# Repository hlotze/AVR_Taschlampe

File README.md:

# AVR_Taschenlampe

Ein ATtiny2313 soll eine RGB-LED per PWM in ihrer Gesamtlichtfarbe beziehungsweise den Helligkeiten der einzelnen Farbkanäle steuern.

## Bedienanleitung

### Einschalten und Ausschalten

Den **ON-Taster drücken und gedrückt halten**. Die Taschenlampe leuchtet mit der zuletzt gespeicherten Farbe und Helligkeit. Bei der ersten Inbetriebnahme nach der Initialprogrammierung sind alle drei Farbkanäle auf den Wert 127 eingestellt.

Zum Ausschalten den ON-Taster loslassen. Nicht gespeicherte Änderungen gehen dabei verloren; beim nächsten Einschalten wird wieder die zuletzt gespeicherte Einstellung verwendet.

### Farbe und Helligkeit einstellen

Den ON-Taster während der gesamten Einstellung gedrückt halten. Die drei Farbkanäle lassen sich unabhängig voneinander verändern:

| Farbkanal | Heller | Dunkler |
|---|---|---|
| Rot | INC_rt | DEC_rt |
| Grün | INC_gn | DEC_gn |
| Blau | INC_bl | DEC_bl |

Ein kurzer Tastendruck erhöht beziehungsweise verringert den jeweiligen Helligkeitswert um 4. Zur Rückmeldung wird der geänderte Farbkanal kurz für etwa 15 ms ausgeschaltet; danach ist seine neue Helligkeit sichtbar. Wird die Taste länger gehalten, beginnt nach etwa einer halben Sekunde die automatische Wiederholung mit ungefähr zehn Änderungen pro Sekunde.

Würde der nächste Schritt über 255 oder unter 0 führen, wird genau der jeweilige Grenzwert erreicht: INC setzt beispielsweise 253 auf 255, DEC setzt 2 auf 0. Damit lässt sich jede Farbe vollständig ausschalten oder auf maximale Helligkeit stellen. Am Grenzwert bleibt der Kanal auch bei weiterem Halten oder erneutem Drücken derselben Taste stehen. Die entgegengesetzte Taste verändert ihn wieder um 4: von 0 auf 4 beziehungsweise von 255 auf 251.

Mehrere Farbkanäle können gleichzeitig eingestellt werden. Werden INC und DEC desselben Kanals gleichzeitig gedrückt, bleibt dieser Kanal unverändert.

Bei jeder tatsächlichen Wertänderung – auch bei automatischer Wiederholung – erhält nur der betroffene Farbkanal diesen kurzen Dunkelimpuls. Andere Farbkanäle bleiben sichtbar. Ist der Endwert bereits erreicht und ändert sich nichts, erfolgt kein weiterer Impuls. Tasterauswertung und Speicherung laufen unabhängig davon weiter; STORE hat Vorrang und behält seine Doppelblinkbestätigung.

### Einzelne Farben beim Einstellen anzeigen

Mit dem Jumper **JP1 (SOLO)** zwischen **PB0, Pin 12, und GND** lässt sich die Anzeige beim Einstellen umschalten:

| JP1 | Anzeige während INC/DEC |
|---|---|
| Offen | Die vollständige Farbmischung bleibt sichtbar. |
| Gesteckt | Nur die Farbkanäle mit gedrückten Einstelltasten sind sichtbar. |

Beispiel: Bei gestecktem JP1 blendet das Halten von INC_rt oder DEC_rt Grün und Blau aus. Rot bleibt sichtbar und wird eingestellt. Sobald die letzte Einstelltaste losgelassen und deren Freigabe entprellt wurde, erscheint wieder die vollständige Mischung mit dem neuen Rotwert. Die Werte der ausgeblendeten Kanäle bleiben erhalten.

Werden mehrere Farbkanäle gleichzeitig eingestellt, sind diese gemeinsam sichtbar. Bei gleichzeitigem INC und DEC eines Kanals bleibt dieser sichtbar, aber sein Wert unverändert. Das Ausblenden funktioniert auch dann, wenn der bearbeitete Kanal bereits seinen Grenzwert erreicht hat. Tasten, die beim Einschalten gehalten und noch nicht freigegeben wurden, lösen keine Einzelanzeige aus.

Der Jumper wird laufend ausgewertet und kann während des Betriebs geändert werden. STORE speichert unabhängig vom Modus immer die tatsächlichen Werte aller drei Farbkanäle. Die Doppelblinkbestätigung verwendet weiterhin alle drei Farben.

### Einstellung speichern

1. Die gewünschte Farbe und Helligkeit einstellen und die Einstelltasten loslassen. ON weiterhin gedrückt halten.
2. **STORE einmal drücken**.
3. Die Bestätigung abwarten: Die LED blinkt zweimal mit der vorgesehenen Weißmischung und zeigt danach wieder die eingestellte Farbe. ON bis zum Ende dieser Bestätigung gedrückt halten.
4. Anschließend kann ON losgelassen werden. Die Einstellung wird beim nächsten Einschalten wiederhergestellt.

Wenn die aktuelle Einstellung bereits gespeichert ist, bewirkt STORE keine erneute Speicherung und die LED blinkt nicht. Längeres Gedrückthalten von STORE löst keine zusätzlichen Speichervorgänge aus.

Während des Speicherns und Blinkens werden die Bedientasten ignoriert. Für weitere Änderungen gegebenenfalls noch gehaltene Einstelltasten oder STORE zuerst loslassen und erneut drücken. Das gilt auch für Tasten, die bereits beim Einschalten gehalten wurden.

### Test auf dem Evaluationboard

Diese Bedienanleitung beschreibt die eigenständig versorgte Taschenlampe. Beim Test mit dem ATtiny auf dem Evaluationboard schaltet der ON-Taster am Steckbrett nur die LED-Versorgung. Der Mikrocontroller läuft weiter; das Einschalten mit erneutem Laden der gespeicherten Werte wird dort durch einen Reset am Evaluationboard getestet. Anschluss- und Programmierhinweise stehen in der [Firmware-Anleitung](firmware/README.md).

## Funktion

### Stromversorgung

Die Schaltung wird mit drei AAA-Batterien zu je 1,5 V betrieben. Die Nennspannung beträgt somit 4,5 V.

### ON Taster

Der ON-Taster schließt den positiven 4,5-V-Zweig und versorgt die gesamte Schaltung einschließlich des ATtiny2313 mit Spannung. Die Taschenlampe leuchtet nur, solange der ON-Taster gehalten wird.

Beim Einschalten werden die Helligkeitswerte für Rot, Grün und Blau aus dem internen EEPROM gelesen und gemäß den unter „internes EEPROM“ beschriebenen Regeln geprüft. Die Einzel-LEDs erhalten die entsprechenden PWM-Signale. Lichtblitze beim Einschalten sollen vermieden werden.

Nach dem Einschalten wird ausschließlich die gespeicherte beziehungsweise bei einem Speicherfehler die vorgesehene Ersatzhelligkeit des jeweiligen Farbkanals ausgegeben; vorher bleiben alle Farbkanäle aus.

Beim Einschalten bereits gedrückte INC-, DEC- und STORE-Taster werden erst nach dem Loslassen und einem erneuten Drücken ausgewertet.

Beim Loslassen des ON-Tasters erlischt die LED. Änderungen, die nicht mit STORE gespeichert wurden, gehen verloren.

### Common-Anode LED

Die Common-Anode-LED besteht aus drei Einzel-LEDs mit gemeinsamer Anode: jeweils einer für Rot, Grün und Blau.

Der Helligkeitswert jedes Farbkanals liegt zwischen 0 (vollständig aus) und 255 (vollständig an).

Die PWM-Frequenz ist bei der Firmware-Konfiguration einstellbar. Ein durch eine zu niedrige PWM-Frequenz verursachtes Flimmern ist bei Bedarf durch Anpassen dieser Konfiguration zu beheben. Mit „Anwender“ ist hierbei die Person gemeint, die die Firmware konfiguriert und programmiert.

### Taster für Helligkeitswerte der Einzel-LEDs

Für jeden Farbkanal gibt es einen Taster zum Erhöhen (INC) und einen zum Verringern (DEC) der Helligkeit:

- INC_rt, DEC_rt
- INC_gn, DEC_gn
- INC_bl, DEC_bl

Alle Taster außer dem ON-Taster sind zu entprellen. Dies gilt auch für STORE.

Ein entprellter Tastendruck verändert den Helligkeitswert des jeweiligen Kanals sofort um +4 (INC) beziehungsweise −4 (DEC) Einheiten. Zur optischen Schrittrückmeldung wird die PWM-Ausgabe nur dieses Kanals für etwa 15 ms auf 0 gesetzt und anschließend der neue Wert ausgegeben. Die Rückmeldung blockiert die Tasterauswertung nicht und wird nur bei einer tatsächlichen Wertänderung ausgelöst.

Die Helligkeit wird in Schritten von ±4 verändert und auf den Wertebereich 0 bis 255 begrenzt. Würde INC über 255 hinausführen, wird auf 255 gesetzt; würde DEC unter 0 führen, wird auf 0 gesetzt. Der letzte Schritt darf dadurch kleiner als 4 sein. Beispiele: INC verändert 253 auf 255, DEC verändert 2 auf 0. Auch ausgehend vom Startwert 127 werden beide Endwerte erreicht. Weiteres Halten oder erneutes Drücken derselben Taste lässt den Grenzwert unverändert. Die Gegenrichtung arbeitet von dort mit einem vollen Schritt weiter: INC von 0 auf 4, DEC von 255 auf 251. Es erfolgt kein Umlauf.

Nach 500 ms Gedrückthalten wird die Änderung alle 100 ms wiederholt, bis die Taste losgelassen wird.

Verschiedene Farbkanäle lassen sich gleichzeitig einstellen. Sind INC und DEC desselben Kanals gleichzeitig gedrückt, bleibt dieser Kanal unverändert; andere Kanäle werden weiterhin ausgewertet.

### Jumper für die Einzelkanalanzeige

JP1 verbindet PB0 (DIP-Pin 12) mit GND. Der Eingang nutzt den internen Pull-up; offen entspricht HIGH und der bisherigen Mischanzeige, gesteckt entspricht LOW und der Einzelkanalanzeige während INC/DEC. PB1 bleibt frei.

Die Firmware wertet JP1 in jedem Bedienzyklus aus. Bei gestecktem JP1 werden nur Kanäle mit entprellten, freigegebenen und gehaltenen INC-/DEC-Tasten ausgegeben; alle übrigen PWM-Ausgänge werden vorübergehend auf 0 gesetzt. Ohne aktive Einstelltaste wird die volle Mischung ausgegeben. Die zugrunde liegenden RGB-Werte werden durch diese Anzeigeauswahl nicht verändert. Speichern und Blinkbestätigung behalten Vorrang; danach gelten weiterhin die Regeln zur erneuten Tastenfreigabe.

### Store Taster

Der STORE-Taster dient zum dauerhaften Speichern der aktuellen Helligkeitswerte für Rot, Grün und Blau im internen EEPROM. Erst nach dem Speichern stehen geänderte Werte beim nächsten Einschalten wieder zur Verfügung.

Beim Drücken von STORE werden die aktuellen Werte aller drei Kanäle als gemeinsamer Stand übernommen. Falls gleichzeitig eine Helligkeitsänderung erkannt wird, wird zuerst diese Änderung ausgeführt und anschließend gespeichert.

Die Speicherung wird nur ausgelöst, wenn sich aktuelle Werte von den gespeicherten Werten unterscheiden. Stimmen alle Werte überein, wird weder geschrieben noch eine Blinkbestätigung ausgegeben. Für ungültige EEPROM-Einträge gilt die unter „internes EEPROM“ beschriebene Ausnahme.

Pro Tastendruck wird höchstens einmal gespeichert und einmal durch doppeltes Blinken bestätigt, auch wenn STORE länger gedrückt bleibt.

Während des Speicherns und der Blinkbestätigung werden INC, DEC und STORE ignoriert. Danach werden noch gehaltene Tasten erst nach dem Loslassen und erneutem Drücken ausgewertet.

Nach erfolgreichem Speichern blinkt die LED zweimal weiß mit RGB (127, 127, 127): jeweils 200 ms an und 200 ms aus. Die Bestätigung funktioniert dadurch auch bei zuvor ausgeschalteten Farbkanälen. Danach werden die aktuellen Helligkeitswerte wieder angezeigt.

Der ON-Taster muss bis zum Ende der Bestätigung gehalten werden. Anschließend kann er losgelassen werden; die neuen Werte sind gespeichert und werden beim nächsten Einschalten verwendet.

### internes EEPROM

Bei der Programmierung des ATtiny2313 werden die initialen Helligkeitswerte im internen EEPROM auf RGB (127, 127, 127) festgelegt.

Beim Einschalten werden die gespeicherten Werte pro Kanal auf Gültigkeit geprüft. Ein fehlender oder als ungültig erkennbarer Kanalwert wird nur für diesen Kanal durch den Standardwert 127 ersetzt. Sind alle drei Werte ungültig, ergibt sich RGB (127, 127, 127).

Nach einem unterbrochenen Speichervorgang wird mit den vorliegenden gültigen EEPROM-Werten gearbeitet. Dabei dürfen gültige alte und neue Kanalwerte gemeinsam verwendet werden. Ein unvollständig geschriebener oder beschädigter Kanalwert muss als ungültig erkennbar sein und wird durch 127 ersetzt. Der Zahlenwert 255 allein gilt nicht als Fehler, da er zum erlaubten Wertebereich gehört.

Ersatzwerte werden zunächst nur für den laufenden Betrieb verwendet. Erst ein erneuter STORE-Tastendruck speichert sie dauerhaft. Dabei gilt ein ungültiger EEPROM-Eintrag als Abweichung, auch wenn der Ersatzwert bereits 127 beträgt.

## Umsetzung

### Schaltplan

[KiCad-Schaltplan](hardware/AVR_Taschenlampe.kicad_sch) auf DIN A4 im Querformat, [KiCad-Projekt](hardware/AVR_Taschenlampe.kicad_pro) und [Vorschau](hardware/preview/AVR_Taschenlampe.svg).

Details zu Pinbelegung, Bauteilen, LED-Auswahl und Prüfung stehen in der [Schaltungsdokumentation](hardware/README.md).

### Platinenlayout

[Belegungsplan für 24 × 18 Löcher im Hochformat](hardware/lochraster-24x18-hochformat.md) mit Lochkoordinaten und Drahtliste. Die [Zeichnung](hardware/lochraster-24x18-hochformat.svg) zeigt die Bestückungsseite, die gespiegelte Lötseite und den Drahtverlauf von oben. Zum Umplatzieren und Entflechten gibt es ein [editierbares KiCad-Board](hardware/lochraster-24x18-hochformat.kicad_pcb).

### Codierung

[Firmware und Anleitung zum Bauen und Programmieren](firmware/README.md), [Programmcode](firmware/src/main.c).

Die erste Version für den ATtiny2313 enthält RGB-PWM, Tasterbedienung und EEPROM-Speicherung. Flash- und EEPROM-Dateien werden getrennt erzeugt; Am 16.11.2026 hat der Anwender auf dem Evaluationboard die Helligkeitsänderung je Farbkanal über INC/DEC, das Speichern mit STORE einschließlich Doppelblinken sowie die Wiederherstellung der zuletzt gespeicherten Farbe nach RESET erfolgreich geprüft.

## Programmierung und Testaufbau 

- mit Pollin Evaluationboard und Portsplitter
  - ATtiny2313
  - RGB-LED, jede Farbe wird über eigenen Transistor angesteuert
  - 6 Taster für INC & DEC der Helligkeit jeder Farbe rot, grün, blau
  - Store-Taster, zum Speicher der Helligkeitswerte in ATtiny internen EEPROM

## weitere Dokumentation

siehe im Verzeichnis [docs](docs/docs.md)

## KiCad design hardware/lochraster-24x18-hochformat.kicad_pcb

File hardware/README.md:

# Schaltplan AVR-Taschenlampe

Der Schaltplan liegt im nativen KiCad-Format auf einem A4-Blatt im Querformat vor. Das Projekt wurde mit KiCad 10.0.8 erstellt.

- [KiCad-Projekt](AVR_Taschenlampe.kicad_pro)
- [Editierbarer Schaltplan](AVR_Taschenlampe.kicad_sch)
- [A4-Vorschau als SVG](preview/AVR_Taschenlampe.svg)
- [A4-Vorschau als PNG, 300 dpi](preview/AVR_Taschenlampe.png)
- [Elektrische Regelprüfung](erc.json)
- [Exportierte Netzliste](AVR_Taschenlampe.net)

Gleiche Netzbezeichnungen verbinden die räumlich getrennten Schaltungsteile elektrisch. Die Symbole und Beschriftungen sind gegenüber der ersten Fassung um etwa 30 % vergrößert. Die vergrößerten Symbole liegen in der Projektbibliothek `Taschenlampe.kicad_sym` und sind zusätzlich im Schaltplan eingebettet. Ihre Anschlussenden liegen weiterhin auf dem üblichen 50-mil-Raster. Die Bibliothekstabellen verwenden die Standardvariablen von KiCad 10.

## Aufbau

BT1 ist der Anschluss für drei AAA-Zellen in Reihe. SW1 (ON) schaltet ausschließlich den positiven Versorgungszweig. C1 (100 nF) gehört beim Layout unmittelbar an VCC und GND von U1; C2 (1 µF, ungepolt) puffert zusätzlich. Es gibt keine Selbsthaltung der Versorgung.

U1 ist ein ATtiny2313-20PU im DIP-20-Gehäuse. Das eingebettete KiCad-Symbol ATtiny2313V-10P besitzt dieselbe DIP-Pinbelegung; der Bestückungswert bezeichnet den vorgesehenen ATtiny2313-20PU. Der interne RC-Oszillator wird auf 1 MHz konfiguriert; ein externer Quarz ist nicht vorgesehen. Brown-out-Erkennung auf 2,7 V aktivieren, RESET und ISP aktiviert lassen, CKOUT deaktiviert lassen. Die konkreten Fuse-Bytes sind bei der Firmware-Erstellung anhand der tatsächlich eingesetzten Variante festzulegen.

D1 ist eine kleine RGB-LED mit gemeinsamer Anode. Q1–Q3 (BC547B) schalten deren Kathoden gegen Masse. Jede Farbe besitzt einen eigenen Vorwiderstand. Die Basispulldowns R8–R10 halten die Treiber auch während Reset und Programmierung ausgeschaltet. Die Firmware muss die PWM-Ausgänge vor der Aktivierung auf LOW setzen; ein HIGH-Pegel schaltet die jeweilige Farbe ein.

## Pinbelegung

| Funktion | Port | DIP-Pin |
|---|---|---:|
| Rot PWM | PB4 / OC1B | 16 |
| Grün PWM | PB3 / OC1A | 15 |
| Blau PWM | PB2 / OC0A | 14 |
| INC_rt | PD0 | 2 |
| DEC_rt | PD1 | 3 |
| INC_gn | PD2 | 6 |
| DEC_gn | PD3 | 7 |
| INC_bl | PD4 | 8 |
| DEC_bl | PD5 | 9 |
| STORE | PD6 | 11 |
| JP1 / SOLO | PB0 | 12 |
| RESET | PA2 | 1 |
| ISP MOSI | PB5 | 17 |
| ISP MISO | PB6 | 18 |
| ISP SCK | PB7 | 19 |
| VCC / GND | – | 20 / 10 |

Die sieben Bedientaster SW2–SW8 schalten gegen Masse. Interne Pull-ups aktivieren; gedrückt entspricht LOW. Entprellung, Wiederholung und die Behandlung gleichzeitig gedrückter Tasten erfolgen in der Firmware. Die ISP-Leitungen werden nicht durch Taster oder LED-Treiber belastet.

Timer 0 liefert Blau. Timer 1 liefert Grün und Rot und muss dafür im 8-Bit-PWM-Modus betrieben werden. Die Einstellung von PWM-Frequenz und Endwerten 0/255 ist Aufgabe der Firmware.

## JP1 / SOLO

JP1 besitzt zwei Pins: 1 = `SOLO_N` an U1/PB0 (DIP-Pin 12), 2 = GND. Der interne Pull-up wird in der Firmware aktiviert; es ist kein zusätzlicher Widerstand erforderlich. Offen bleibt die Mischung beim Einstellen sichtbar. Gesteckt werden während INC/DEC nur die bearbeiteten Farbkanäle angezeigt; nach Loslassen erscheint die Mischung wieder. Die RGB-Sollwerte bleiben erhalten, STORE speichert weiterhin alle drei Kanäle. Mehrere bearbeitete Kanäle sind gemeinsam sichtbar. Die Jumperstellung wird laufend ausgewertet. PB1 (Pin 13) bleibt unbeschaltet.

Für den Evaluationboard-Test PB0 am Portsplitter verwenden (Extension-Port J4, Pin 9) und JP1 gegen die gemeinsame Masse schalten. JP1 dieses Schaltplans ist nicht mit dem gleichnamigen UART-Jumper auf dem Pollin-Evaluationboard zu verwechseln.

## Bauteile und Dimensionierung

| Referenzen | Wert / Typ | Zweck |
|---|---|---|
| BT1 | 3 × AAA, nominell 4,5 V | Batteriehalteranschluss |
| SW1–SW8 | Schließertaster | ON und sieben Bedientaster |
| U1 | ATtiny2313-20PU | Steuerung, internes EEPROM |
| D1 | RGB, gemeinsame Anode | LED, konkreter Typ noch auszuwählen |
| Q1–Q3 | BC547B, C/B/E = Pins 1/2/3 | Kathodentreiber |
| R1 | 10 kΩ | RESET-Pull-up |
| R2–R4 | je 100 Ω, 0,25 W, 5 % oder besser | LED-Strombegrenzung |
| R5–R7 | je 1 kΩ | Basisstrombegrenzung |
| R8–R10 | je 100 kΩ | Basis-Emitter-Pulldown |
| C1 | 100 nF, Keramik, mindestens 10 V | Abblockung |
| C2 | 1 µF, Keramik, mindestens 10 V | Versorgungspuffer |
| J1 | AVR-ISP, 2 × 3, 2,54 mm | Programmierung |
| JP1 | Jumper, 1 × 2, 2,54 mm | Einzelkanalanzeige: PB0 nach GND |

Mit 100 Ω ergeben sich bei 4,5 V und angenommenen 0,2 V am Transistor rechnerisch etwa 23 mA für Rot bei 2,0 V LED-Durchlassspannung und 13 mA für Grün und Blau bei 3,0 V. Vor der Bestückung die zulässigen Ströme je Kanal anhand des LED-Datenblatts prüfen. Die tatsächlichen Ströme und die optische Weißmischung hängen vom LED-Typ ab.

Vor Bestückung sind LED-Typ, zulässige Ströme und Pinfolge festzulegen. Das Symbol nimmt 1 = Rot-Kathode, 2 = gemeinsame Anode, 3 = Grün-Kathode und 4 = Blau-Kathode an. Deshalb hat D1 noch keinen verbindlichen Footprint. Auch der Batteriehalter benötigt nach mechanischer Auswahl einen Footprint oder Anschluss. Die übrigen Footprints sind Vorschläge für bedrahtete Bauteile.

Der Mikrocontroller arbeitet bei 1 MHz im vorgesehenen Spannungsbereich; für den Entwurf wird eine Versorgung oberhalb der Brown-out-Schwelle bis etwa 4,8 V angenommen. Bei sinkender Batteriespannung nimmt die LED-Helligkeit ab; Grün und Blau können früher ausfallen. Eine geregelte, batteriezustandsunabhängige Helligkeit ist nicht vorgesehen.

## ISP und EEPROM

J1: 1 = MISO, 2 = VCC_SW, 3 = SCK, 4 = MOSI, 5 = RESET, 6 = GND. Beim Programmieren ON gedrückt halten. Der Programmer muss die Zielspannung berücksichtigen und darf die Schaltung nicht zusätzlich versorgen. Mit langsamem ISP-Takt beginnen, beispielsweise 125 kHz bei 1 MHz CPU-Takt.

Es gibt keinen Versorgungspuffer, der einen vollständigen EEPROM-Schreibvorgang nach Loslassen von ON garantiert. Die Firmware muss deshalb die vereinbarte Behandlung unterbrochener Schreibvorgänge umsetzen: pro Kanal einen prüfbaren Datensatz vorsehen, gültige alte/neue Werte zulassen und ungültige Werte durch 127 ersetzen. Eine Integritätsprüfung erkennt Fehler nur entsprechend ihrer Prüfstärke; eine absolute Erkennung beliebiger Beschädigungen ist nicht garantiert. Die Schaltung allein stellt diese Softwareanforderung nicht sicher.

## Prüfung und Grenzen

KiCad ERC: **0 Fehler und 0 Warnungen**, ohne ausgeschlossene Meldungen. Die exportierte Netzliste wurde mit `python3 tools/check_netlist.py` aus dem Projektverzeichnis gegen die beabsichtigten Pin-Netz-Zuordnungen geprüft. Die A4-Vorschau wurde visuell kontrolliert. Der Anwender hat am 16.11.2026 INC/DEC, STORE mit Doppelblinken und die Wiederherstellung nach RESET am Evaluationboard bestätigt. Die am 17.11.2026 ergänzte JP1-Funktion ist noch nicht am Aufbau getestet; elektrische Messungen und eine Schaltungssimulation stehen ebenfalls aus. Ein Platinenlayout ist nicht Bestandteil dieses Schaltplans.

Quellen: [Microchip ATtiny2313/V Datenblatt](https://ww1.microchip.com/downloads/en/DeviceDoc/Atmel-2543-AVR-ATtiny2313_Datasheet.pdf), [onsemi BC547-Datenblatt](https://www.onsemi.com/pdf/datasheet/bc546-d.pdf).

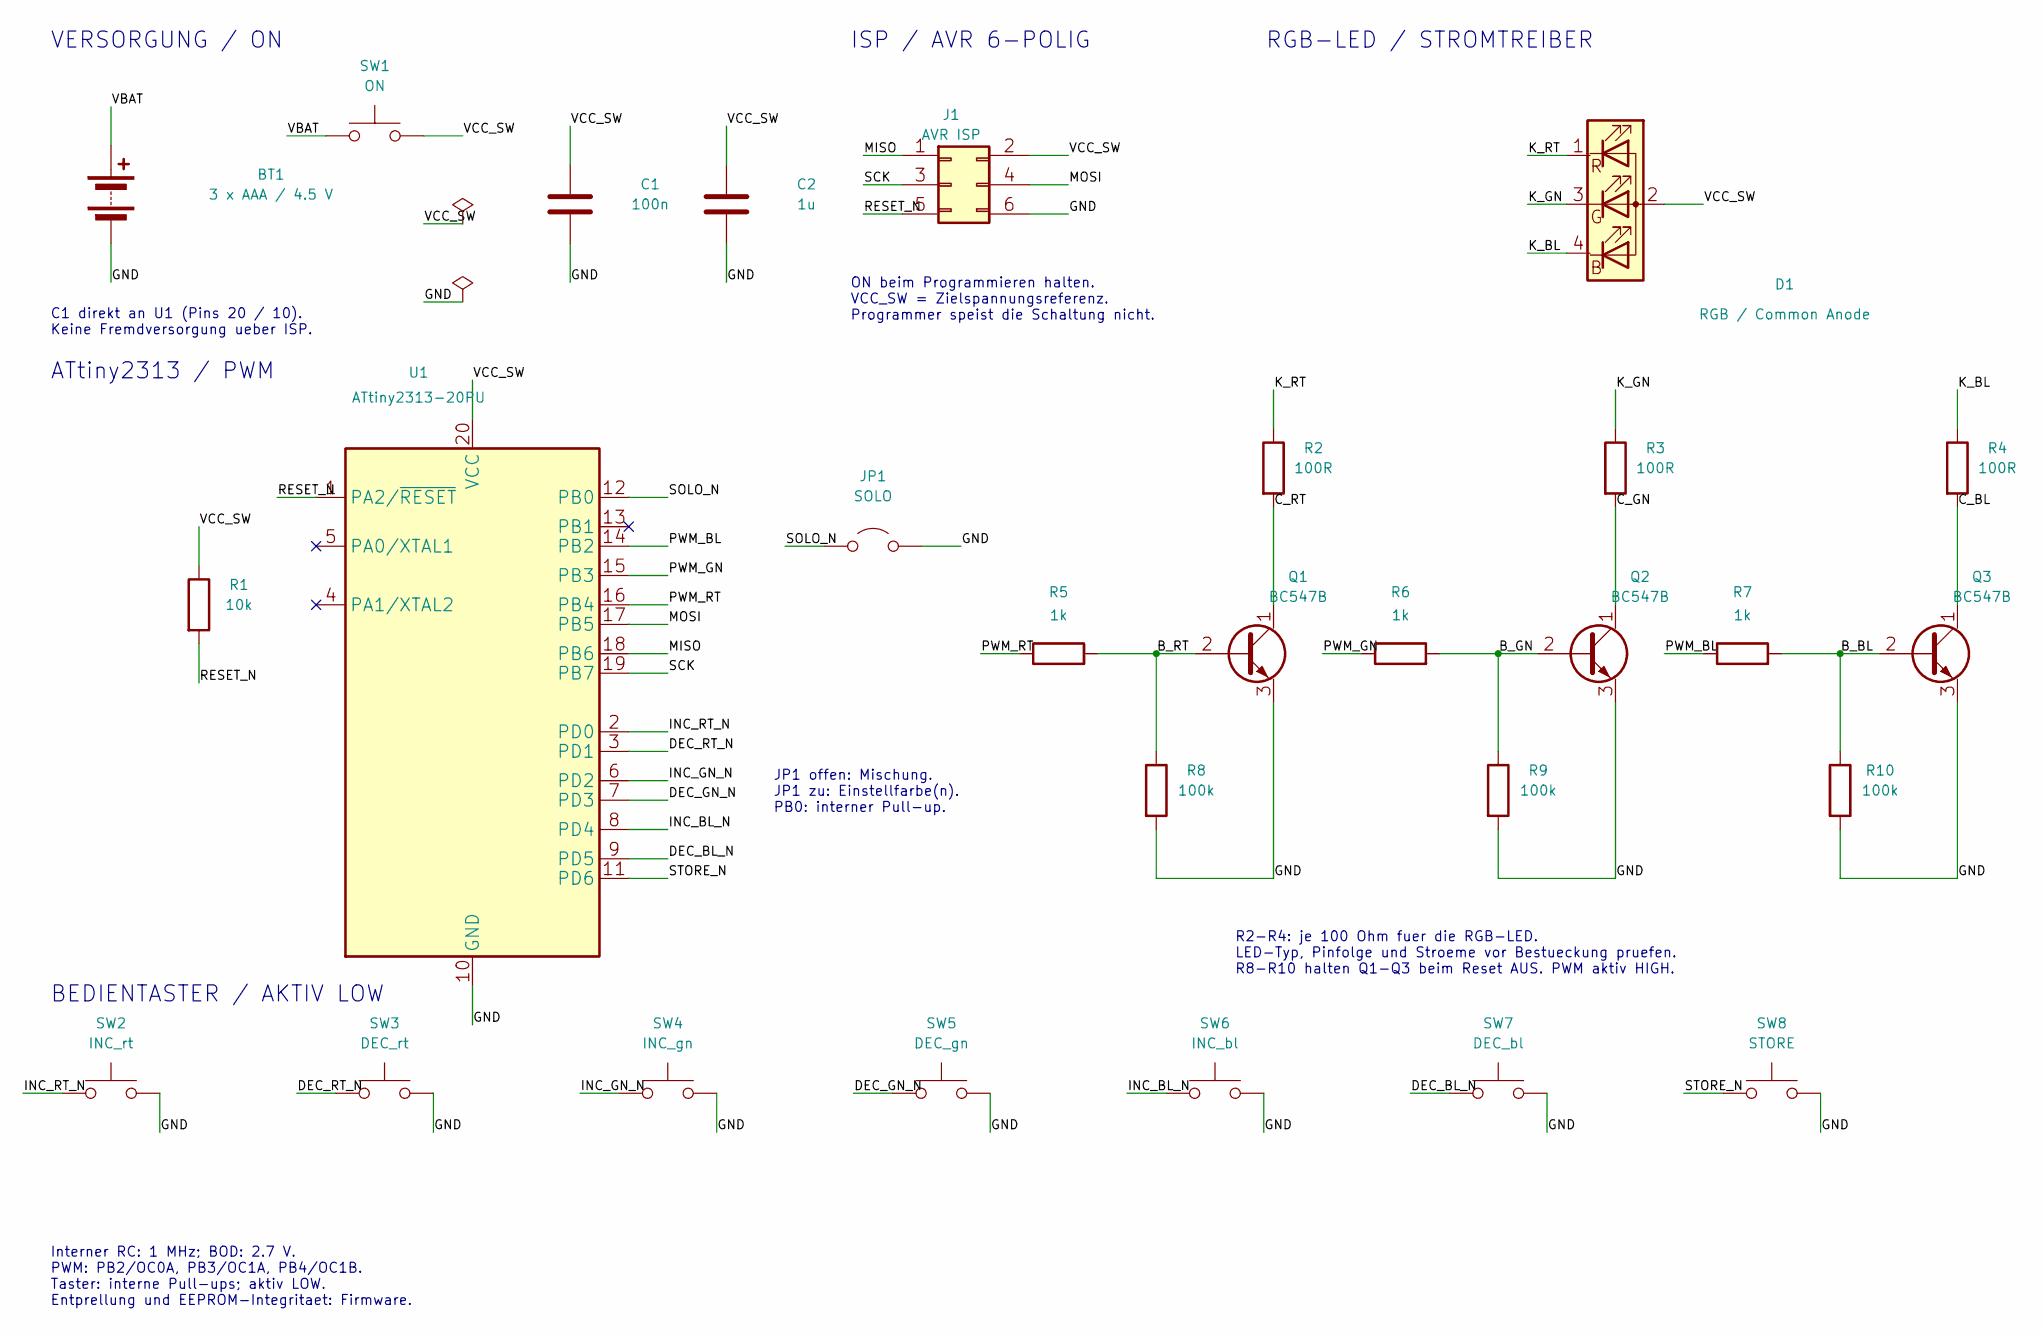
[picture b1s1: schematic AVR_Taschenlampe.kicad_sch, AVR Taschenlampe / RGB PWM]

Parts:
BT1: 3 x AAA / 4.5 V
C1: 100n; C_Disc_D5.0mm_W2.5mm_P5.00mm
C2: 1u; C_Disc_D5.0mm_W2.5mm_P5.00mm
D1: RGB / Common Anode
J1: AVR ISP; IDC-Header_2x03_P2.54mm_Vertical
JP1: SOLO; PinHeader_1x02_P2.54mm_Vertical
Q1, Q2, Q3: BC547B; TO-92_Inline
R1: 10k; R_Axial_DIN0207_L6.3mm_D2.5mm_P10.16mm_Horizontal
R2, R3, R4: 100R; R_Axial_DIN0207_L6.3mm_D2.5mm_P10.16mm_Horizontal
R5, R6, R7: 1k; R_Axial_DIN0207_L6.3mm_D2.5mm_P10.16mm_Horizontal
R8, R9, R10: 100k; R_Axial_DIN0207_L6.3mm_D2.5mm_P10.16mm_Horizontal
SW1: ON; SW_PUSH_6mm
SW2: INC_rt; SW_PUSH_6mm
SW3: DEC_rt; SW_PUSH_6mm
SW4: INC_gn; SW_PUSH_6mm
SW5: DEC_gn; SW_PUSH_6mm
SW6: INC_bl; SW_PUSH_6mm
SW7: DEC_bl; SW_PUSH_6mm
SW8: STORE; SW_PUSH_6mm
U1: ATtiny2313-20PU; DIP-20_W7.62mm

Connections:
B_BL: Q3.2 (B), R7.2, R10.1
B_GN: Q2.2 (B), R6.2, R9.1
B_RT: Q1.2 (B), R5.2, R8.1
C_BL: Q3.1 (C), R4.2
C_GN: Q2.1 (C), R3.2
C_RT: Q1.1 (C), R2.2
DEC_BL_N: SW7.1, U1.9 (PD5)
DEC_GN_N: SW5.1, U1.7 (PD3)
DEC_RT_N: SW3.1, U1.3 (PD1)
GND: BT1.2 (-), C1.2, C2.2, J1.6, JP1.2 (B), Q1.3 (E), Q2.3 (E), Q3.3 (E), R8.2, R9.2, R10.2, SW2.2, SW3.2, SW4.2, SW5.2, SW6.2, SW7.2, SW8.2, U1.10 (GND); also elsewhere on the board
INC_BL_N: SW6.1, U1.8 (PD4)
INC_GN_N: SW4.1, U1.6 (PD2)
INC_RT_N: SW2.1, U1.2 (PD0)
K_BL: D1.4 (BK), R4.1
K_GN: D1.3 (GK), R3.1
K_RT: D1.1 (RK), R2.1
MISO: J1.1, U1.18 (PB6)
MOSI: J1.4, U1.17 (PB5)
PWM_BL: R7.1, U1.14 (PB2)
PWM_GN: R6.1, U1.15 (PB3)
PWM_RT: R5.1, U1.16 (PB4)
RESET_N: J1.5, R1.2, U1.1 (PA2/~RESET)
SCK: J1.3, U1.19 (PB7)
SOLO_N: JP1.1 (A), U1.12 (PB0)
STORE_N: SW8.1, U1.11 (PD6)
VBAT: BT1.1 (+), SW1.1
VCC_SW: C1.1, C2.1, D1.2 (A), J1.2, R1.1, SW1.2, U1.20 (VCC)

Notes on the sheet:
VERSORGUNG / ON
C1 direkt an U1 (Pins 20 / 10). Keine Fremdversorgung ueber ISP.
ATtiny2313 / PWM
JP1 offen: Mischung. JP1 zu: Einstellfarbe(n). PB0: interner Pull-up.
Interner RC: 1 MHz; BOD: 2.7 V. PWM: PB2/OC0A, PB3/OC1A, PB4/OC1B. Taster: interne Pull-ups; aktiv LOW. Entprellung und EEPROM-Integritaet: Firmware.
ISP / AVR 6-POLIG
ON beim Programmieren halten. VCC_SW = Zielspannungsreferenz. Programmer speist die Schaltung nicht.
RGB-LED / STROMTREIBER
R2-R4: je 100 Ohm fuer die RGB-LED. LED-Typ, Pinfolge und Stroeme vor Bestueckung pruefen. R8-R10 halten Q1-Q3 beim Reset AUS. PWM aktiv HIGH.
BEDIENTASTER / AKTIV LOW

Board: 2 copper layers, 31 parts (0 on the bottom side), 24 nets, no tracks yet.

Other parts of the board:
TP1: Masseabgriff; TP1
TP2: Masseabgriff; TP2
TP3: Masseabgriff; TP3
TP4: Masseabgriff; TP4

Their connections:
GND: TP1.1, TP2.1, TP3.1, TP4.1; also elsewhere on the board

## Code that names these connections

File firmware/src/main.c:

#include <avr/io.h>
#include <avr/eeprom.h>
#include <avr/wdt.h>
#include <avr/power.h>
#include <avr/interrupt.h>
#include <util/atomic.h>
#include "control.h"
#include "storage.h"

#define SOLO_PIN PB0
#define PWM_PINS (_BV(PB2) | _BV(PB3) | _BV(PB4))
/* The .eep output programs this data separately from Flash. */
uint8_t EEMEM initial_levels[EEPROM_BYTES] = {
    127, 128, COMMITTED, 127, 128, COMMITTED, 127, 128, COMMITTED
};
static Control control;
static volatile uint8_t tick_ready;
static volatile uint8_t overflow_count;

/* Keep UI timing tied to hardware, even while the main loop computes. */
ISR(TIMER0_OVF_vect)
{
    if (++overflow_count >= POLL_DIVIDER) {
        overflow_count = 0;
        tick_ready = 1;
    }
}

static void restart_ticks(void)
{
    ATOMIC_BLOCK(ATOMIC_RESTORESTATE) {
        tick_ready = 0;
        overflow_count = 0;
        TIFR = _BV(TOV0);
    }
}

/* AVR-libc recommended early watchdog shutdown; .init3 falls through. */
void early_watchdog_off(void) __attribute__((naked, used, section(".init3")));
void early_watchdog_off(void)
{
    MCUSR = 0;
    wdt_disable();
}

uint8_t storage_read_byte(uint8_t address)
{
    return eeprom_read_byte(&initial_levels[address]);
}

void storage_write_byte(uint8_t address, uint8_t value)
{
    eeprom_update_byte(&initial_levels[address], value);
    eeprom_busy_wait(); /* A write returns before the physical burn completes. */
}

static void pwm_set(uint8_t red, uint8_t green, uint8_t blue)
{
    OCR0A = blue;
    OCR1A = green;
    OCR1B = red;
}

static void show_current_levels(void)
{
    uint8_t visible[CHANNELS];
    control_display(&control, !(PINB & _BV(SOLO_PIN)), visible);
    pwm_set(visible[0], visible[1], visible[2]);
}

static void pwm_init(void)
{
    /* NPN stages are active HIGH. Keep all outputs LOW until levels are loaded. */
    PORTB &= (uint8_t)~PWM_PINS;
    DDRB |= PWM_PINS;
    TCCR0A = _BV(WGM00); /* Phase correct, TOP = 255; 0/255 are fully OFF/ON. */
    TCCR0B = 0;
    TCCR1A = _BV(WGM10); /* Timer 1 mode 1: phase correct 8 bit. */
    TCCR1B = 0;
    TCNT0 = 0;
    TCNT1 = 0;
    pwm_set(control.level[0], control.level[1], control.level[2]);
    TCCR0A |= _BV(COM0A1);
    TCCR1A |= _BV(COM1A1) | _BV(COM1B1);
#if PWM_PRESCALER == 1
    TCCR0B = _BV(CS00);
    TCCR1B = _BV(CS10);
#else
    TCCR0B = _BV(CS01);
    TCCR1B = _BV(CS11);
#endif
    TIFR = _BV(TOV0);
    TIMSK = _BV(TOIE0);
}

static void wait_tick(void)
{
    while (!tick_ready) {}
    tick_ready = 0;
}

static void wait_blink_phase(void)
{
    for (uint8_t i = 0; i < BLINK_TICKS; ++i)
        wait_tick();
}

static void confirm_store(void)
{
    restart_ticks(); /* Discard ticks accumulated during EEPROM writes. */
    for (uint8_t i = 0; i < 2; ++i) {
        pwm_set(127, 127, 127);
        wait_blink_phase();
        pwm_set(0, 0, 0);
        wait_blink_phase();
    }
    pwm_set(control.level[0], control.level[1], control.level[2]);
}

int main(void)
{
    /* Assumes oscillator fuse selects internal 8 MHz RC, not a board crystal. */
#if F_CPU == 1000000UL
    clock_prescale_set(clock_div_8);
#else
    clock_prescale_set(clock_div_1);
#endif
    PORTB &= (uint8_t)~PWM_PINS;
    DDRB |= PWM_PINS;
    DDRB &= (uint8_t)~_BV(SOLO_PIN);
    PORTB |= _BV(SOLO_PIN); /* JP1: PB0 to GND enables isolated channel preview. */
    DDRD &= (uint8_t)~BUTTON_MASK;
    PORTD |= BUTTON_MASK; /* PD0..PD6: switches to GND, internal pull-ups. */
    storage_load(control.level);
    control_reset_buttons(&control);
    pwm_init();
    sei();
    for (;;) {
        wait_tick();
        uint8_t store = control_tick(&control, (uint8_t)~PIND & BUTTON_MASK);
        show_current_levels();
        if (store) {
            /* STORE takes priority: do not stretch a 15-ms impulse while writing. */
            for (uint8_t c = 0; c < CHANNELS; ++c)
                control.dark[c] = 0;
            pwm_set(control.level[0], control.level[1], control.level[2]);
            uint8_t result = storage_store(control.level);
            if (result == 1)
                confirm_store();
            if (result != 0) {
                /* Ignore all keys until a fresh debounced release after STORE. */
                control_reset_buttons(&control);
                restart_ticks();
            }
        }
    }
}
